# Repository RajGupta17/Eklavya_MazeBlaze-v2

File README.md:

# Eklavya_MazeBlaze-v2
In this project, we will be working on Improvising PCB design and Sensor Placements of MazeBlaze bot and Implement a better maze solving algorithm on the MazeBlaze bot and attain maximum speed while traversing.

Our Main aim is to design an algorithm , which will enable us to map the entire maze and hence give us the shortest path. Further , we plan to improvize the design by trying new components and trying new sensore placements etc . 

The end goal of our project is to form a Maze-solving and a line-following bot , which can find the shortest path in the maze.

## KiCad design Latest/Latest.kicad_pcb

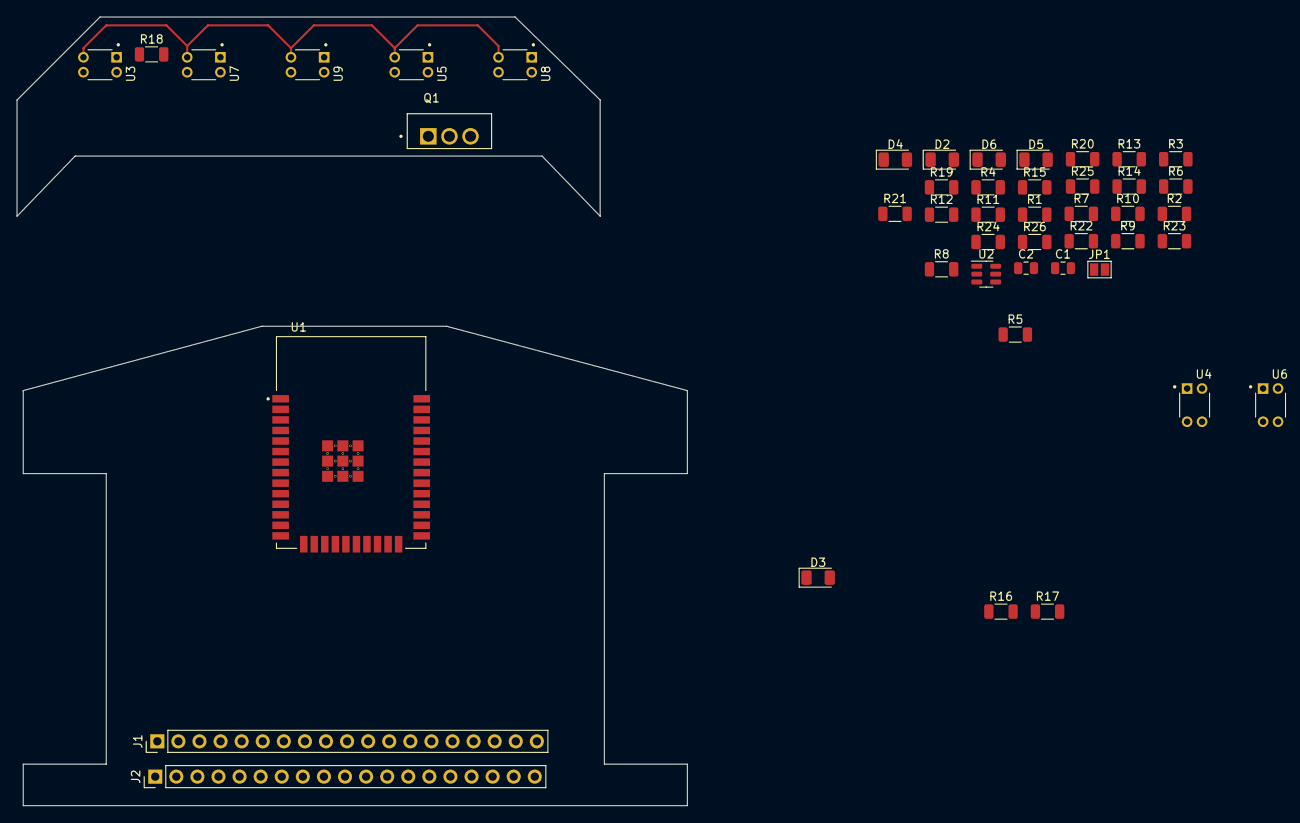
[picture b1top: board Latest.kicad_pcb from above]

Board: 2 copper layers, 80.8 x 95.0 mm, 46 parts (0 on the bottom side), 44 nets.

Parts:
C1, C2: 22uF; C_0805_2012Metric
D2, D3, D4, D5, D6: LED; LED_1206_3216Metric
J1, J2: Conn_01x19_Male; PinHeader_1x19_P2.54mm_Vertical
JP1: SolderJumper_2_Open; SolderJumper-2_P1.3mm_Open_Pad1.0x1.5mm
Q1: IRFZ44N; TO254P1016X419X2286-3
R1: 2.2K; R_1206_3216Metric
R2, R3, R4, R5, R6, R7, R8, R9, R10, R11, R12, R13, R14, R15, R16, R17, R18, R19, R20, R21, R22, R23, R24, R25, R26: R; R_1206_3216Metric
U1: ESP32-DEVKITC-32D; MODULE_ESP32-WROOM-32
U2: MT3608; SOT-23-6
U3, U4, U5, U6, U7, U8, U9: TCRT5000; DIP400W50P180L360H200Q4

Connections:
3V3: J1.1, R6.1, R7.1, R8.1, R9.1, R10.1, R11.1, R12.1, R13.1, R14.1, R15.1, R18.1, R19.1, R20.1, R21.1, R26.1, U1.1 (3V3)
+V: C2.1, JP1.1 (A), R25.2
A1: J1.10, R4.2, U1.10 (IO26)
A2: J1.11, R5.2, U1.11 (IO27)
An1: J1.9, R15.2, U1.9 (IO25)
An2: J1.8, R7.2, U1.8 (IO33)
An3: J1.7, R9.2, U1.7 (IO32)
An4: J1.6, R13.2, U1.6 (IO35)
An5: J1.5, R19.2, U1.5 (IO34)
An6: J1.4, R21.2, U1.4 (SENSOR_VN)
An7: J1.3, R11.2, U1.3 (SENSOR_VP)
B1: J1.12, R3.2, U1.12 (IO14)
B2: J1.13, R2.2, U1.13 (IO12)
END_LED: J1.17, R22.2, R23.1, R24.1, U1.17 (SD3)
GND: C1.2, C2.2, D2.1 (K), D3.1 (K), D4.1 (K), D5.1 (K), D6.1 (K), J1.14, J2.13, J2.19, Q1.3, R1.2, R17.1, U1.14 (GND1), U1.20 (GND3), U1.26 (GND2), U2.2 (GND)
unnamed: D2.2 (A), R22.1
unnamed: D3.2 (A), R23.2
unnamed: D4.2 (A), R24.2
unnamed: D5.2 (A), R25.1
unnamed: D6.2 (A), R26.2
unnamed: J1.2, U1.2 (EN)
unnamed: J1.15, U1.15 (IO13)
unnamed: J1.16, U1.16 (SD2)
unnamed: J1.18, U1.18 (CMD)
unnamed: J2.1, U1.38 (CLK)
unnamed: J2.2, U1.37 (SD0)
unnamed: J2.3, U1.36 (SD1)
unnamed: J2.4, U1.35 (IO15)
unnamed: J2.6, U1.33 (IO0)
unnamed: J2.8, U1.31 (IO16)
unnamed: J2.9, U1.30 (IO17)
unnamed: J2.10, U1.29 (IO5)
unnamed: J2.11, U1.28 (IO18)
unnamed: J2.12, U1.27 (IO19)
unnamed: J2.15, U1.24 (RXD0)
unnamed: J2.16, U1.23 (TXD0)
unnamed: J2.18, U1.21 (IO23)
unnamed: Q1.1, R16.2, R17.2
PWMA: J2.7, R16.1, U1.32 (IO4)
PWMB: J2.5, U1.34 (IO2)
SCL_OLED: J2.17, U1.22 (IO22)
SDA_OLED: J2.14, U1.25 (IO21)
SWO: C1.1, U2.4 (EN), U2.5 (IN)
Vin_ESP: J1.19, JP1.2 (B), U1.19 (EXT_5V)

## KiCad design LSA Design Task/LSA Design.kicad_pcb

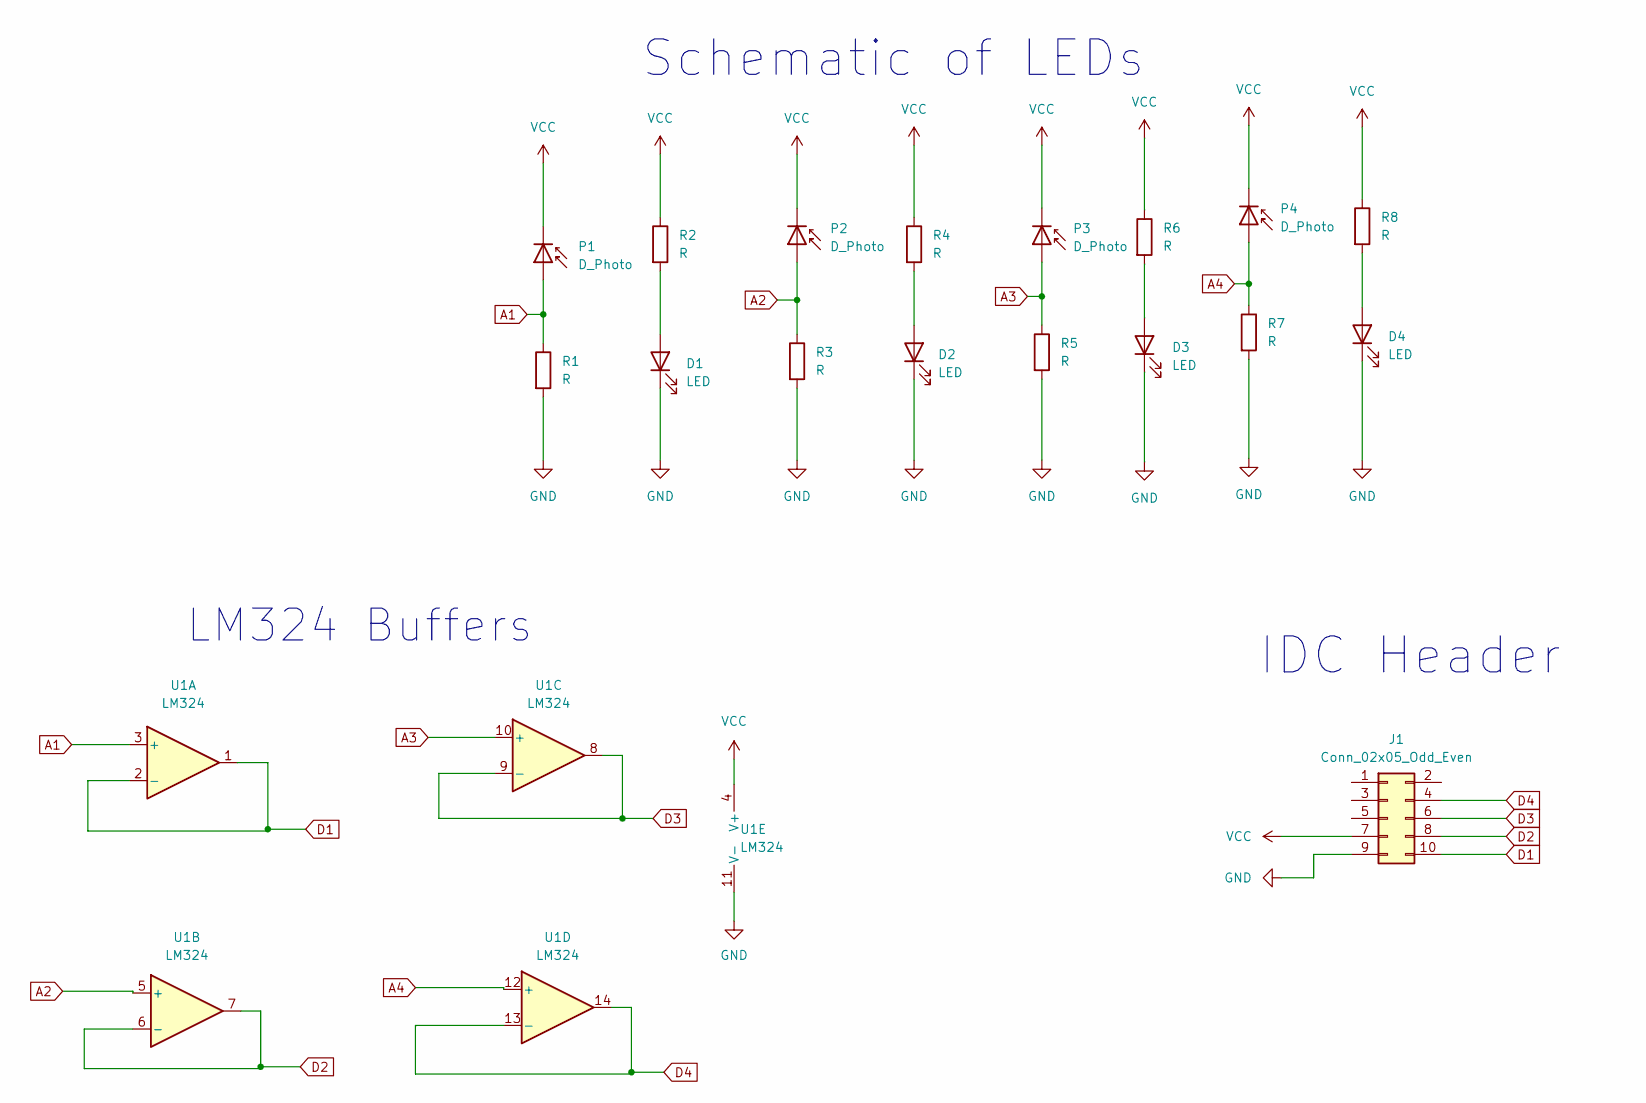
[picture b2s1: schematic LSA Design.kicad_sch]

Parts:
D1, D2, D3, D4: LED; LED_D3.0mm
J1: Conn_02x05_Odd_Even; IDC-Header_2x05_P2.54mm_Vertical
P1, P2, P3, P4: D_Photo; LED_D5.0mm
R1, R2, R3, R4, R5, R6, R7, R8: R; R_Axial_DIN0207_L6.3mm_D2.5mm_P10.16mm_Horizontal
U1: LM324; DIP794W45P254L1969H508Q14

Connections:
A1: P1.2 (A), R1.1, U1.3 (+)
A2: P2.2 (A), R3.1, U1.5 (+)
A3: P3.2 (A), R5.1, U1.10 (+)
A4: P4.2 (A), R7.1, U1.12 (+)
D1: J1.10, U1.1, U1.2 (-)
D2: J1.8, U1.6 (-), U1.7
D3: J1.6, U1.8, U1.9 (-)
D4: J1.4, U1.13 (-), U1.14
GND: D1.1 (K), D2.1 (K), D3.1 (K), D4.1 (K), J1.9, R1.2, R3.2, R5.2, R7.2, U1.11 (V-)
unnamed: D1.2 (A), R2.2
unnamed: D2.2 (A), R4.2
unnamed: D3.2 (A), R6.2
unnamed: D4.2 (A), R8.2
VCC: J1.7, P1.1 (K), P2.1 (K), P3.1 (K), P4.1 (K), R2.1, R4.1, R6.1, R8.1, U1.4 (V+)

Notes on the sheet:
Schematic of LEDs
IDC Header
LM324 Buffers

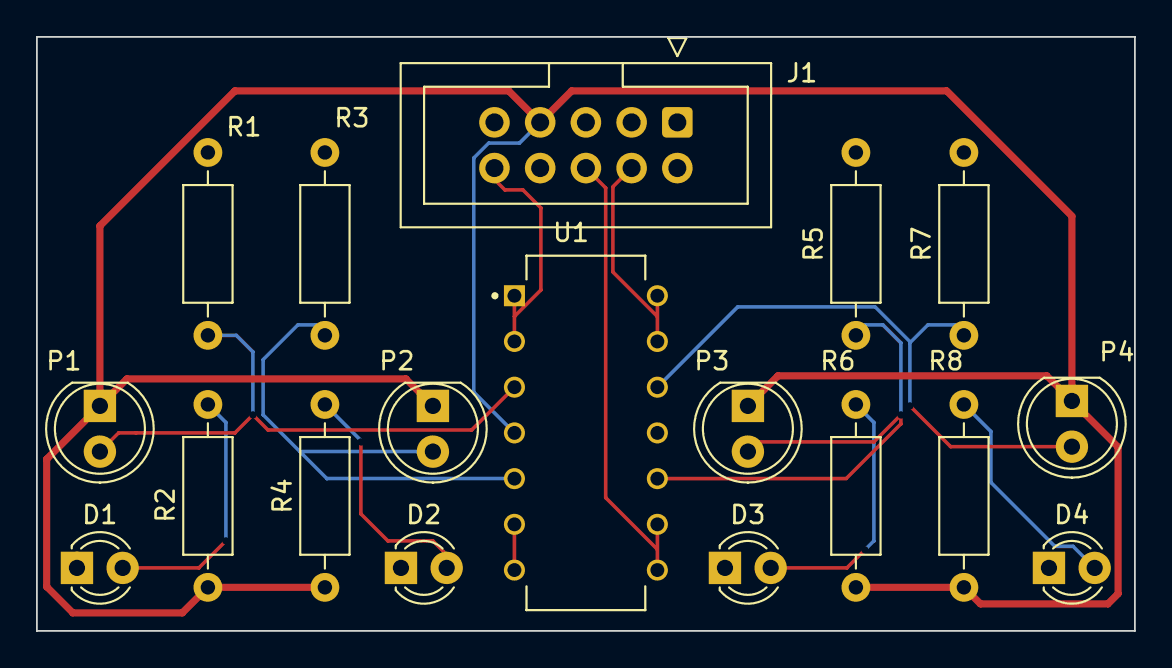
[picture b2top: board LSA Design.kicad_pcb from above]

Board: 2 copper layers, 61.0 x 33.0 mm, 18 parts (0 on the bottom side), 14 nets.

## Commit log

2022-08-18 Create KiCAD
2022-08-18 Update KiCAD
2022-08-18 KiCAD
2022-08-18 Study Material
2022-08-25 KiCAD LSA Task
2022-08-26 Intro to the Project
2022-08-26 Task
2022-08-27 PCB Design Task
2022-08-31 Conceptual Notes
2022-09-01 vault backup: 2022-09-01 12:03:59
2022-09-01 vault backup: 2022-09-01 12:09:20
2022-09-01 vault backup: 2022-09-01 12:26:51
2022-09-01 vault backup: 2022-09-01 12:31:51
2022-09-01 vault backup: 2022-09-01 12:36:51
2022-09-01 vault backup: 2022-09-01 12:41:51
2022-09-01 vault backup: 2022-09-01 12:46:51
2022-09-01 vault backup: 2022-09-01 12:51:51
2022-09-01 vault backup: 2022-09-01 12:56:51
2022-09-01 vault backup: 2022-09-01 13:01:43
2022-09-02 vault backup: 2022-09-03 00:40:49
2022-09-02 vault backup: 2022-09-03 00:45:49
2022-09-09 vault backup: 2022-09-09 10:47:58
2022-09-09 vault backup: 2022-09-09 10:52:57
2022-09-09 Add files via upload
    This is code to count the number of pulses as obtained by quadrature encoder
2022-09-10 Update encoder.c
    modifying the first and fixing syntax errors
2022-09-10 vault backup: 2022-09-11 00:08:13
2022-09-10 encoders
2022-09-10 vault backup: 2022-09-11 00:11:33
2022-09-14 Implementing DFS (Depth - first - search )
    This code will implement the DFS i.e. will map the entire maze and store it in the form or graph i.e. edges and vertices . This code is incomplete for now .
2022-09-14 Description for algorithm
    We plan to use DFS and Dijkstra's algorithm . This file is incomplete for now .
2022-09-14 Description of algorithm used in main.c
2022-09-14 CAD model of the bot
    This represents the Solid works CAD model i.e. structure and design of the bot
2022-09-14 Description of algorithm used
2022-09-16 Implementing DFS
    The code is incomplete yet
2022-09-16 Update main.c
    code incomplete . all variables defined in variable.h header file
2022-09-16 contains all variables definations
2022-09-19 Create embedded
2022-09-19 Embedded C code
    for Line following , turns etc.
2022-09-19 Update lsa.c
    adc channel 2 doesnt allow pin 0 , 4 15 etc to be used
2022-09-19 Embedded C
2022-09-20 Enncoder
2022-09-20 vault backup: 2022-09-20 17:33:49
2022-09-20 Encoder
2022-09-21 Encoder Readings
2022-09-21 vault backup: 2022-09-21 15:00:23
2022-09-22 To read distance from both encoders separately
2022-10-01 lfr redundant path
2022-10-01 LFR logic
    Completed logic
2022-10-01 10_trials
2022-10-01 11_trials
2022-10-02 vault backup: 2022-10-02 12:01:12
2022-12-08 vault backup: 2022-12-08 23:04:34
2022-12-08 vault backup: 2022-12-08 23:09:34
